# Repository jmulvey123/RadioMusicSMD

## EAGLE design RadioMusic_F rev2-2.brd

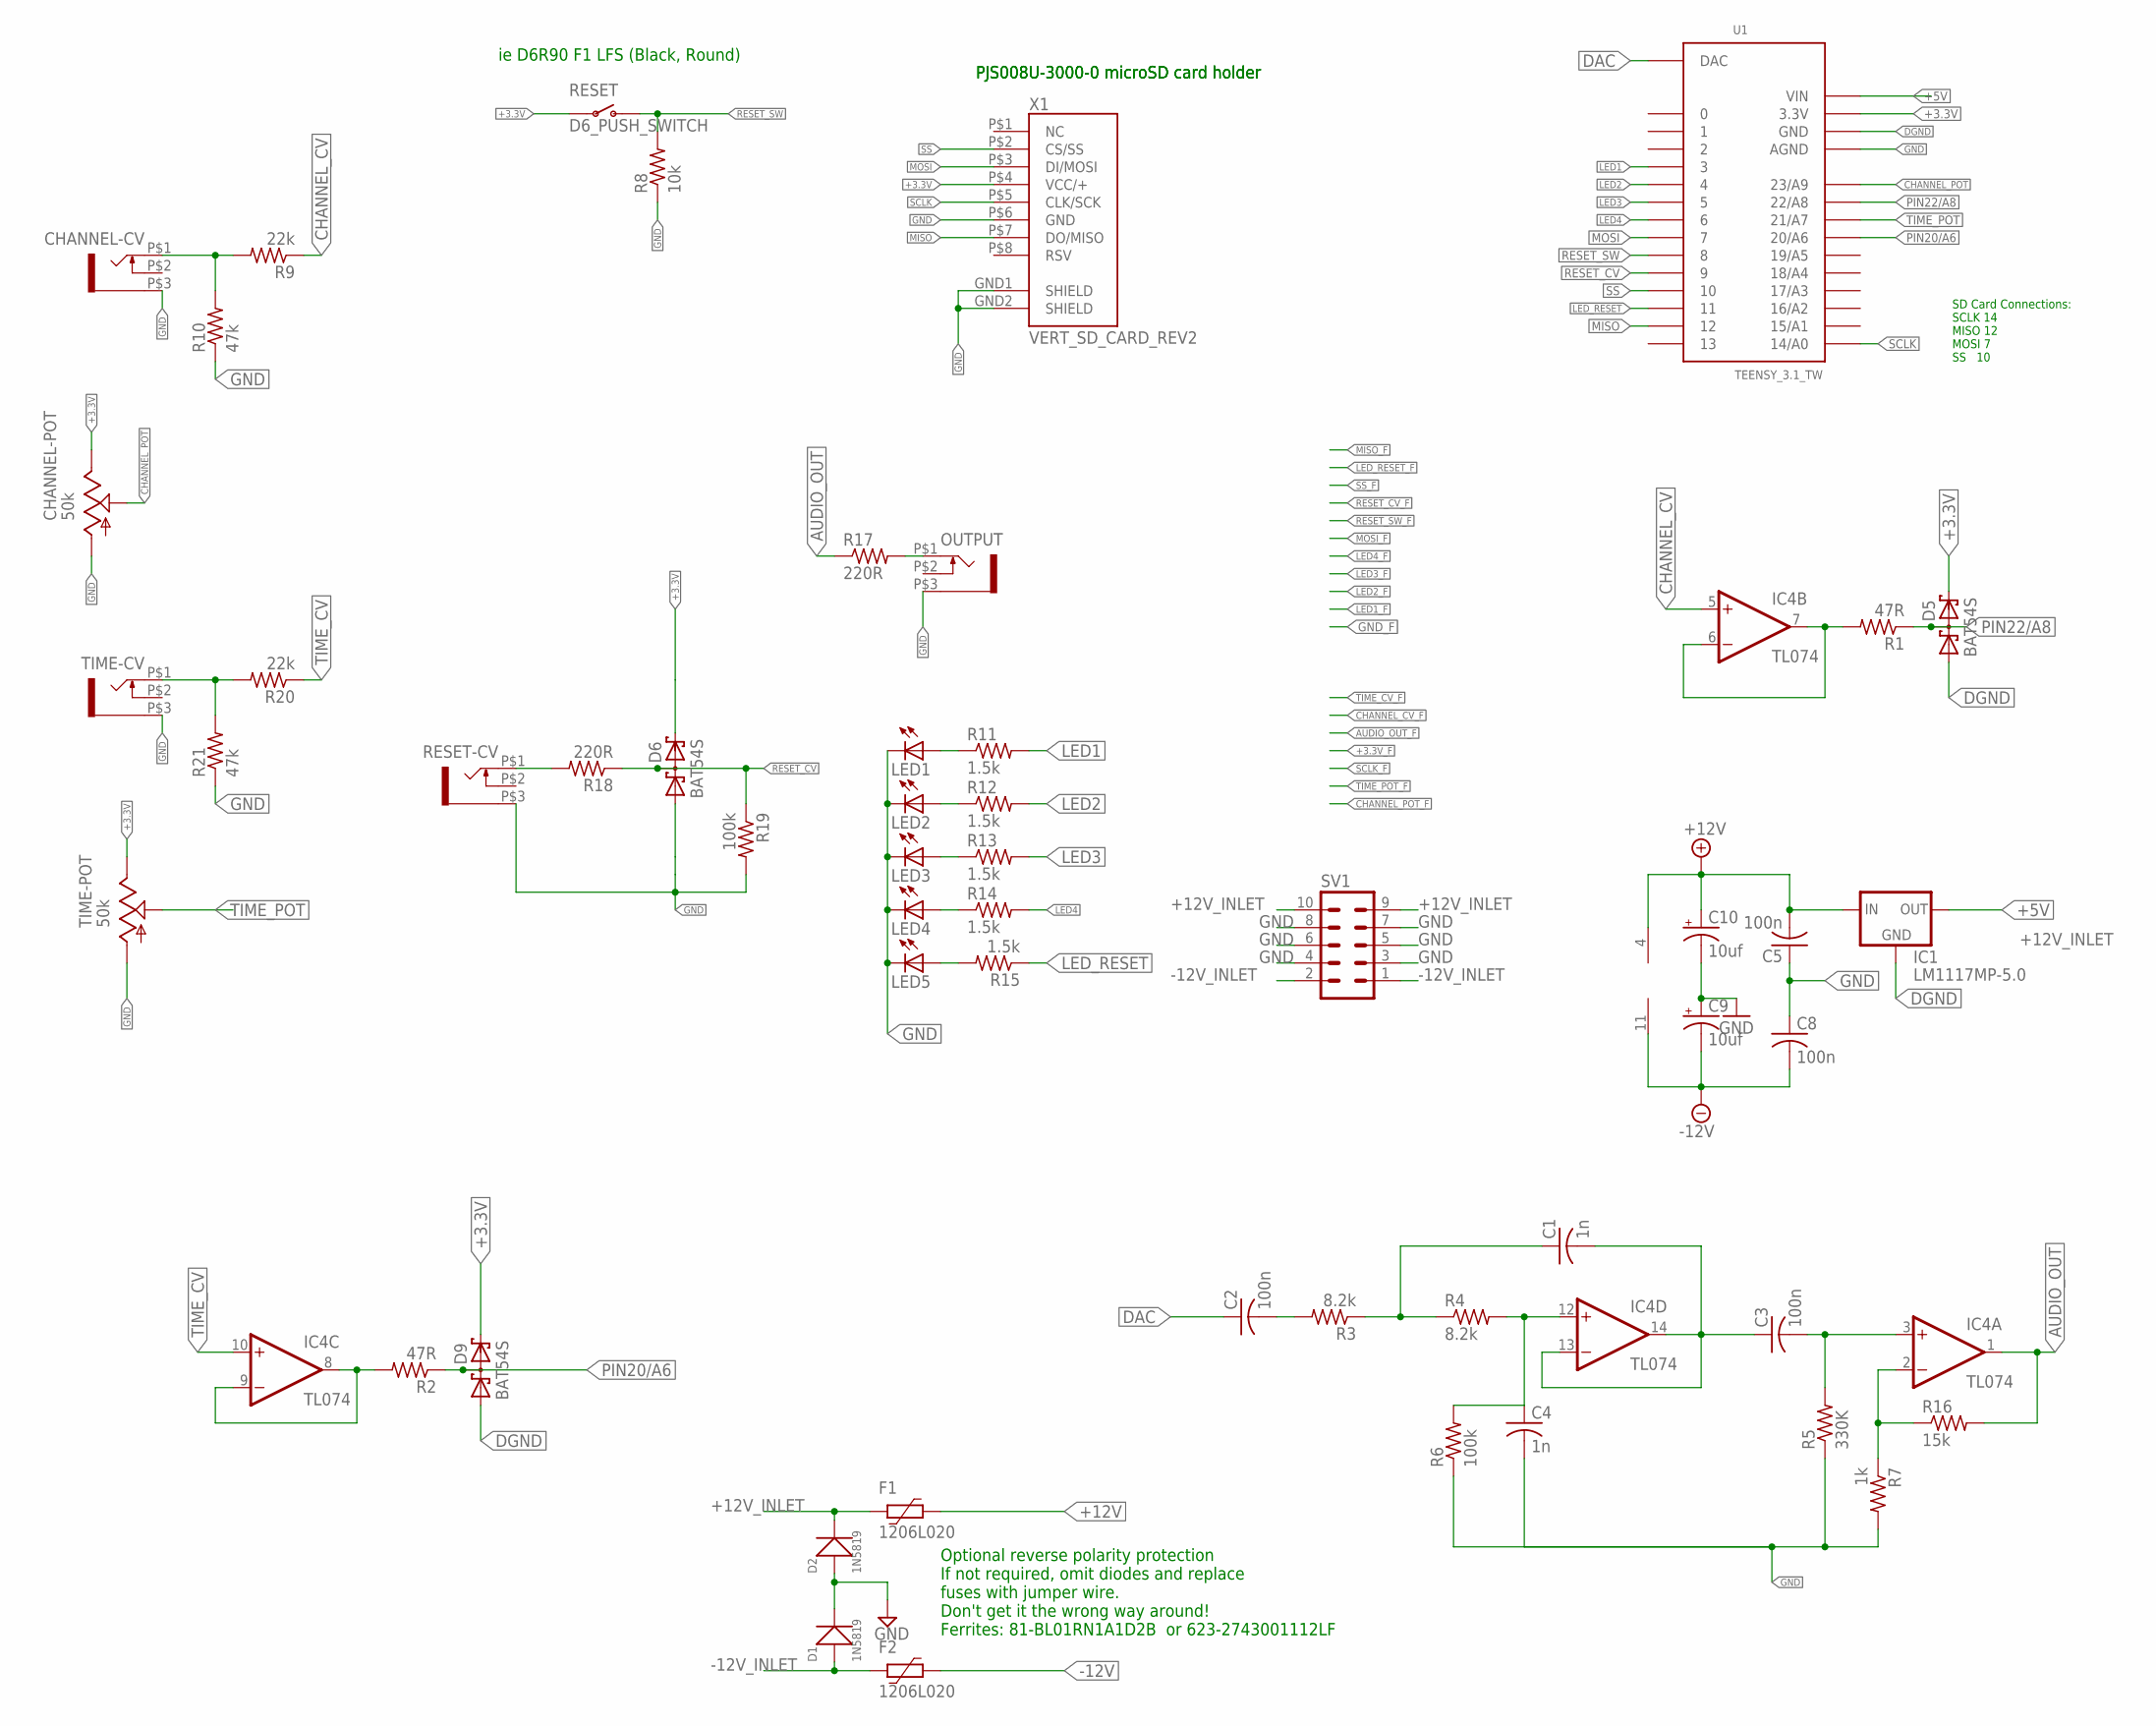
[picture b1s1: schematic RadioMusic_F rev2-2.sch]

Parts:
C1, C4: 1n; C0805
C2, C3, C5, C8: 100n; C0805
C9, C10: 10uf; PANASONIC_B
CHANNEL-CV: WQP-PJ301M-12_JACK
CHANNEL-POT: 50k; EVUF
D1, D2: 1N5819; SOD-123
D5, D6, D9: BAT54S; SOT23
F1, F2: 1206L020; 1206L
IC1: LM1117MP-5.0; SOT223
IC4: TL074; SO14
LED1, LED2, LED3, LED4, LED5: LED3MM
OUTPUT: WQP-PJ301M-12_JACK
R1, R2: 47R; R0805
R3, R4: 8.2k; R0805
R5: 330K; R0805
R6, R19: 100k; R0805
R7: 1k; R0805
R8: 10k; R0805
R9, R20: 22k; R0805
R10, R21: 47k; R0805
R11, R12, R13, R14, R15: 1.5k; R0805
R16: 15k; R0805
R17, R18: 220R; R0805
RESET: D6_PUSH_SWITCH; D6_BUTTON_RND
RESET-CV: WQP-PJ301M-12_JACK
SV1: 10_PIN_HEADER; MA05-2
TIME-CV: WQP-PJ301M-12_JACK
TIME-POT: 50k; EVUF
U1: TEENSY_3.1_TW
X1: VERT_SD_CARD_REV2; VERT_MICROSD_REV2

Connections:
+3.3V: CHANNEL-POT.3 (E), D5.2 (C2), D6.2 (C2), D9.2 (C2), RESET.P$3, RESET.P$4, TIME-POT.3 (E), U1.3.3V, X1.P$4 (VCC/+)
+5V: IC1.2 (OUT), IC1.4 (OUT), U1.VIN
+12V: C5.2, C10.+, F1.1, IC1.3 (IN), IC4.4 (V+)
+12V_INLET: D2.-, F1.2, SV1.9, SV1.10
-12V: C8.2, C9.-, F2.1, IC4.11 (V-)
-12V_INLET: D1.+, F2.2, SV1.1, SV1.2
AUDIO_OUT: IC4.1 (OUT), R16.2, R17.1
CHANNEL_CV: IC4.5 (+IN), R9.1
CHANNEL_POT: CHANNEL-POT.2 (S), U1.23/A9
DAC: C2.1, U1.DAC
DGND: D5.1 (A1), D9.1 (A1), IC1.1 (GND), U1.GND
GND: C4.2, C5.1, C8.1, C9.+, C10.-, CHANNEL-CV.P$3 (1), CHANNEL-POT.1 (A), D1.-, D2.+, D6.1 (A1), LED1.K (C), LED2.K (C), LED3.K (C), LED4.K (C), LED5.K (C), OUTPUT.P$3 (1), R5.1, R6.1, R7.2, R8.1, R10.1, R19.2, R21.1, RESET-CV.P$3 (1), SV1.3, SV1.4, SV1.5, SV1.6, SV1.7, SV1.8, TIME-CV.P$3 (1), TIME-POT.1 (A), U1.AGND, X1.GND1 (SHIELD), X1.GND2 (SHIELD), X1.P$6 (GND)
LED1: R11.2, U1.3
LED2: R12.2, U1.4
LED3: R13.2, U1.5
LED4: R14.2, U1.6
LED_RESET: R15.1, U1.11
MISO: U1.12, X1.P$7 (DO/MISO)
MOSI: U1.7, X1.P$3 (DI/MOSI)
unnamed: IC4.6 (-IN), IC4.7 (OUT), R1.2
unnamed: C4.1, IC4.12 (+IN), R4.2, R6.2
unnamed: OUTPUT.P$1 (2), R17.2
unnamed: C1.1, R3.1, R4.1
unnamed: C1.2, C3.1, IC4.13 (-IN), IC4.14 (OUT)
unnamed: C3.2, IC4.3 (+IN), R5.2
unnamed: IC4.2 (-IN), R7.1, R16.1
unnamed: IC4.8 (OUT), IC4.9 (-IN), R2.2
unnamed: CHANNEL-CV.P$1 (2), R9.2, R10.2
unnamed: C2.2, R3.2
unnamed: LED2.A, R12.1
unnamed: LED4.A, R14.1
unnamed: LED3.A, R13.1
unnamed: R18.2, RESET-CV.P$1 (2)
unnamed: LED1.A, R11.1
unnamed: LED5.A, R15.2
PIN20/A6: D9.3 (C1A2), R2.1, U1.20/A6
PIN22/A8: D5.3 (C1A2), R1.1, U1.22/A8
RESET_CV: D6.3 (C1A2), R18.1, R19.1, U1.9
RESET_SW: R8.2, RESET.P$1 (O), RESET.P$2 (O), U1.8
SCLK: U1.14/A0, X1.P$5 (CLK/SCK)
SS: U1.10, X1.P$2 (CS/SS)
TEMP: R20.2, R21.2, TIME-CV.P$1 (2)
TIME_CV: IC4.10 (+IN), R20.1
TIME_POT: TIME-POT.2 (S), U1.21/A7

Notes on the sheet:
ie D6R90 F1 LFS (Black, Round)
PJS008U-3000-0 microSD card holder
SD Card Connections: SCLK 14 MISO 12 MOSI 7 SS 10
Optional reverse polarity protection If not required, omit diodes and replace fuses with jumper wire. Don't get it the wrong way around! Ferrites: 81-BL01RN1A1D2B or 623-2743001112LF

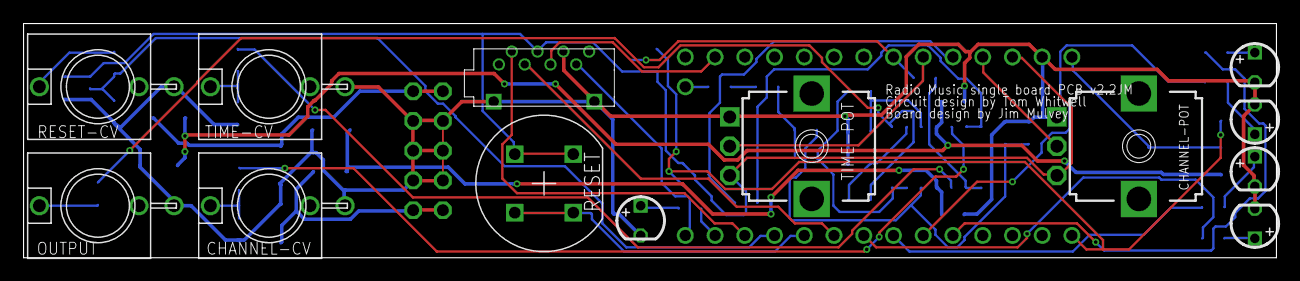
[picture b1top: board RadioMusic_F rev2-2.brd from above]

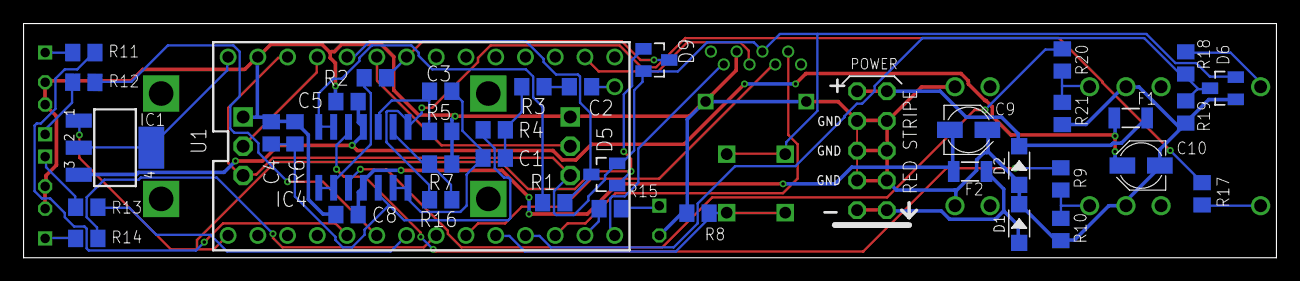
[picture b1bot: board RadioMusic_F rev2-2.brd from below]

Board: 4 copper layers, 107.0 x 20.0 mm, 53 parts (40 on the bottom side), 44 nets.

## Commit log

2020-05-13 Added v2.2 files

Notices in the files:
parts and their libraries:
lm1117: (c) 2014 Samuel Lourenço
